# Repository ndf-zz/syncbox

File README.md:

# syncbox

MIDI/USB to DIN sync converter

[work in progress]

## Contents

   - pcb: Kicad schematic and circuit board
   - enclosure: FreeCAD enclosure
   - firmware: STM32 firmware
   - syncbox-edit: Python SysEx configuration editor

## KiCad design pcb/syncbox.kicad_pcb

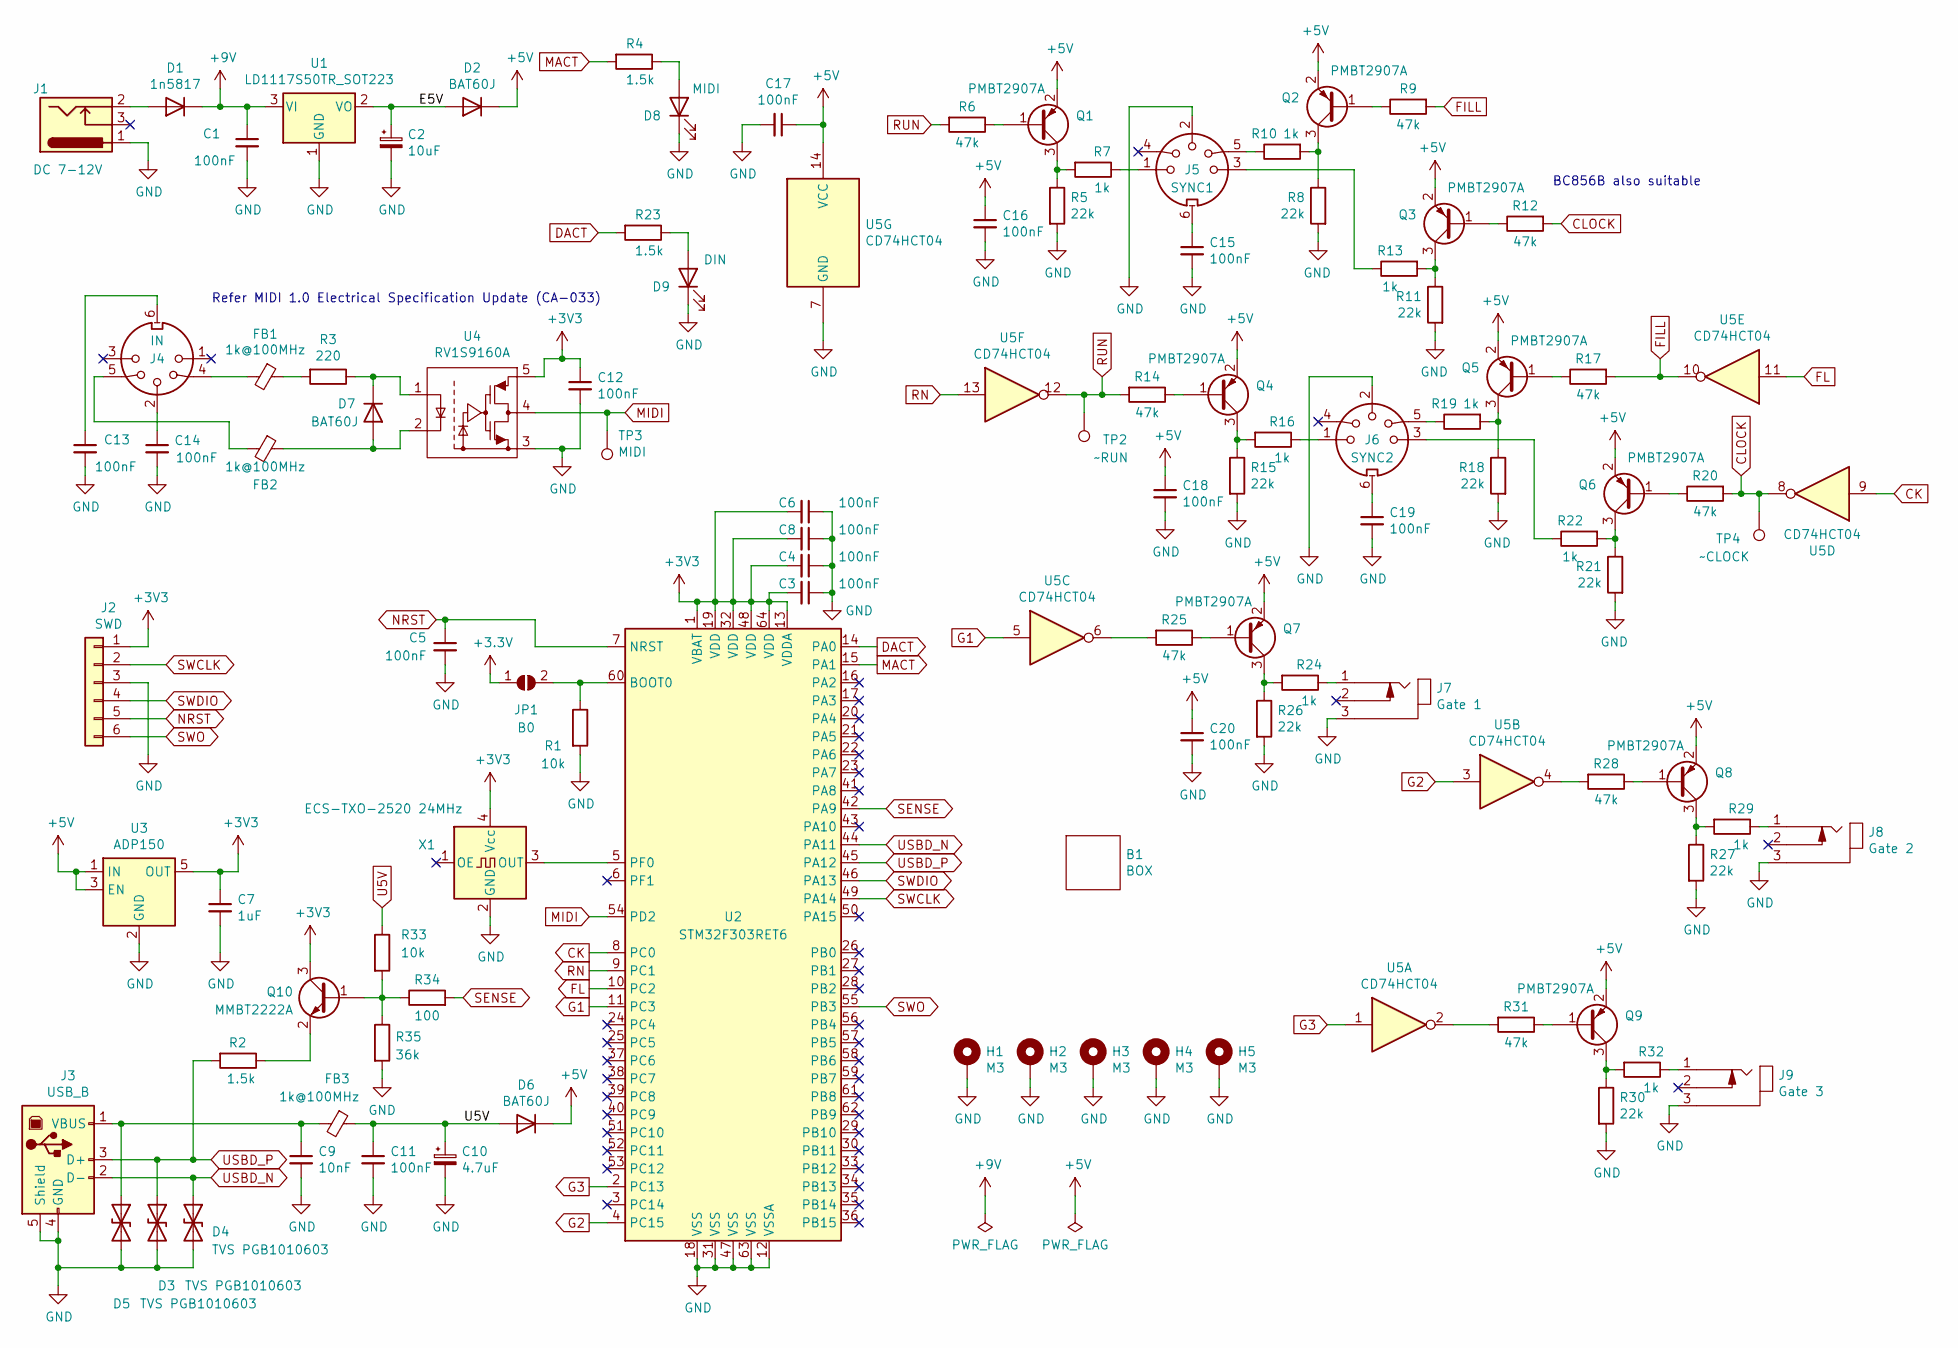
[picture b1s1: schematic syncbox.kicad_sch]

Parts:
B1: BOX
C1, C3, C4, C5, C6, C8, C11, C12, C13, C14, C15, C16, C17, C18, C19, C20: 100nF; C_0805_2012Metric_Pad1.15x1.40mm_HandSolder
C2: 10uF; CP_Radial_D4.0mm_P2.00mm
C7: 1uF; C_0805_2012Metric_Pad1.15x1.40mm_HandSolder
C9: 10nF; C_0805_2012Metric_Pad1.15x1.40mm_HandSolder
C10: 4.7uF; CP_Radial_D4.0mm_P2.00mm
D1: 1n5817; D_A-405_P10.16mm_Horizontal
D2, D6, D7: BAT60J; D_SOD-323_HandSoldering
D3, D4, D5: TVS PGB1010603; D_0603_1608Metric_Pad1.05x0.95mm_HandSolder
D8: MIDI; LED_D3.0mm_Clear
D9: DIN; LED_D3.0mm_Clear
FB1, FB2, FB3: 1k@100MHz; L_0603_1608Metric_Pad1.05x0.95mm_HandSolder
H1, H2, H3, H4, H5: M3; MountingHole_3.2mm_M3_Pad
J1: DC 7-12V; BarrelJack_Horizontal
J2: SWD; PinHeader_1x06_P2.54mm_Vertical
J3: USB_B; MUSBD111M0
J4: IN; 5211450-1
J5: SYNC1; 5211450-1
J6: SYNC2; 5211450-1
J7: Gate 1; 35RAPC2AHN2
J8: Gate 2; 35RAPC2AHN2
J9: Gate 3; 35RAPC2AHN2
JP1: B0; SolderJumper-2_P1.3mm_Open_RoundedPad1.0x1.5mm
Q1, Q2, Q3, Q4, Q5, Q6, Q7, Q8, Q9: PMBT2907A; SOT-23_Handsoldering
Q10: MMBT2222A; SOT-23_Handsoldering
R1: 10k; R_0805_2012Metric_Pad1.15x1.40mm_HandSolder
R2, R4, R23: 1.5k; R_0805_2012Metric_Pad1.15x1.40mm_HandSolder
R3: 220; R_0805_2012Metric_Pad1.15x1.40mm_HandSolder
R5, R8, R11, R15, R18, R21, R26, R27, R30: 22k; R_0805_2012Metric_Pad1.15x1.40mm_HandSolder
R6, R9, R12, R14, R17, R20, R25, R28, R31: 47k; R_0805_2012Metric_Pad1.15x1.40mm_HandSolder
R7, R10, R13, R16, R19, R22, R24, R29, R32: 1k; R_0805_2012Metric_Pad1.15x1.40mm_HandSolder
R33: 10k; R_0805_2012Metric_Pad1.20x1.40mm_HandSolder
R34: 100; R_0805_2012Metric_Pad1.20x1.40mm_HandSolder
R35: 36k; R_0805_2012Metric_Pad1.20x1.40mm_HandSolder
TP2: ~RUN; TestPoint_Pad_D1.5mm
TP3: MIDI; TestPoint_Pad_D1.5mm
TP4: ~CLOCK; TestPoint_Pad_D1.5mm
U1: LD1117S50TR_SOT223; SOT-223-3_TabPin2
U2: STM32F303RET6; LQFP-64_10x10mm_P0.5mm; LCSC C183214
U3: ADP150; SOT-23-5_HandSoldering
U4: RV1S9160A; SO-5_4.4x3.6mm_P1.27mm
U5: CD74HCT04; SOIC-14_3.9x8.7mm_P1.27mm
X1: ECS-TXO-2520 24MHz; Oscillator_SMD_SeikoEpson_SG210-4Pin_2.5x2.0mm_HandSoldering

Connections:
+5V: C16.1, C17.1, C18.1, C20.1, D2.1 (K), D6.1 (K), Q1.2 (E), Q2.2 (E), Q3.2 (E), Q4.2 (E), Q5.2 (E), Q6.2 (E), Q7.2 (E), Q8.2 (E), Q9.2 (E), U3.1 (IN), U3.3 (EN), U5.14 (VCC)
+9V: C1.1, D1.1 (K), U1.3 (VI)
/E5V: C2.1, D2.2 (A), U1.2 (VO)
CK: U2.8 (PC0), U5.9
CLOCK: R12.2, R20.2, TP4.1, U5.8
DACT: R23.2, U2.14 (PA0)
FILL: R9.2, R17.2, U5.10
FL: U2.10 (PC2), U5.11
G1: U2.11 (PC3), U5.5
G2: U2.4 (PC15), U5.3
G3: U2.2 (PC13), U5.1
GND: C1.2, C2.2, C3.1, C4.1, C5.2, C6.1, C7.2, C8.1, C9.2, C10.2, C11.2, C12.2, C13.2, C14.2, C15.2, C16.2, C17.2, C18.2, C19.2, C20.2, D3.2 (A2), D4.2 (A2), D5.2 (A2), D8.1 (K), D9.1 (K), H1.1, H2.1, H3.1, H4.1, H5.1, J1.1, J2.3, J3.4 (GND), J3.5 (Shield), J5.2, J6.2, J7.3, J8.3, J9.3, R1.2, R5.2, R8.2, R11.2, R15.2, R18.2, R21.2, R26.2, R27.2, R30.2, R35.2, U1.1 (GND), U2.12 (VSSA), U2.18 (VSS), U2.31 (VSS), U2.47 (VSS), U2.63 (VSS), U3.2 (GND), U4.3, U5.7 (GND), X1.2 (GND)
MACT: R4.2, U2.15 (PA1)
MIDI: TP3.1, U2.54 (PD2), U4.4
NRST: C5.1, J2.5, U2.7 (NRST)
unnamed: C9.1, D5.1 (A1), FB3.2, J3.1 (VBUS)
unnamed: C13.1, J4.6
unnamed: C14.1, J4.2
unnamed: C15.1, J5.6
unnamed: C19.1, J6.6
unnamed: D1.2 (A), J1.2
unnamed: D7.1 (K), R3.1, U4.1
unnamed: D7.2 (A), FB2.1, U4.2
unnamed: D8.2 (A), R4.1
unnamed: D9.2 (A), R23.1
unnamed: FB1.1, R3.2
unnamed: FB1.2, J4.4
unnamed: FB2.2, J4.5
unnamed: J5.1, R7.1
unnamed: J5.3, R13.1
unnamed: J5.5, R10.1
unnamed: J6.1, R16.1
unnamed: J6.3, R22.1
unnamed: J6.5, R19.1
unnamed: J7.1, R24.1
unnamed: J8.1, R29.1
unnamed: J9.1, R32.1
unnamed: JP1.2 (B), R1.1, U2.60 (BOOT0)
unnamed: Q1.1 (B), R6.1
unnamed: Q1.3 (C), R5.1, R7.2
unnamed: Q2.1 (B), R9.1
unnamed: Q2.3 (C), R8.1, R10.2
unnamed: Q3.1 (B), R12.1
unnamed: Q3.3 (C), R11.1, R13.2
unnamed: Q4.1 (B), R14.1
unnamed: Q4.3 (C), R15.1, R16.2
unnamed: Q5.1 (B), R17.1
unnamed: Q5.3 (C), R18.1, R19.2
unnamed: Q6.1 (B), R20.1
unnamed: Q6.3 (C), R21.1, R22.2
unnamed: Q7.1 (B), R25.1
unnamed: Q7.3 (C), R24.2, R26.1
unnamed: Q8.1 (B), R28.1
unnamed: Q8.3 (C), R27.1, R29.2
unnamed: Q9.1 (B), R31.1
unnamed: Q9.3 (C), R30.1, R32.2
unnamed: Q10.1 (B), R33.2, R34.1, R35.1
unnamed: Q10.2 (E), R2.1
unnamed: R25.2, U5.6
unnamed: R28.2, U5.4
unnamed: R31.2, U5.2
unnamed: U2.5 (PF0), X1.3 (OUT)
RN: U2.9 (PC1), U5.13
RUN: R6.2, R14.2, TP2.1, U5.12
SENSE: R34.2, U2.42 (PA9)
SWCLK: J2.2, U2.49 (PA14)
SWDIO: J2.4, U2.46 (PA13)
SWO: J2.6, U2.55 (PB3)
U5V: C10.1, C11.1, D6.2 (A), FB3.1, R33.1
USBD_N: D4.1 (A1), J3.2 (D-), U2.44 (PA11)
USBD_P: D3.1 (A1), J3.3 (D+), R2.2, U2.45 (PA12)

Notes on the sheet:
Refer MIDI 1.0 Electrical Specification Update (CA-033)
BC856B also suitable

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
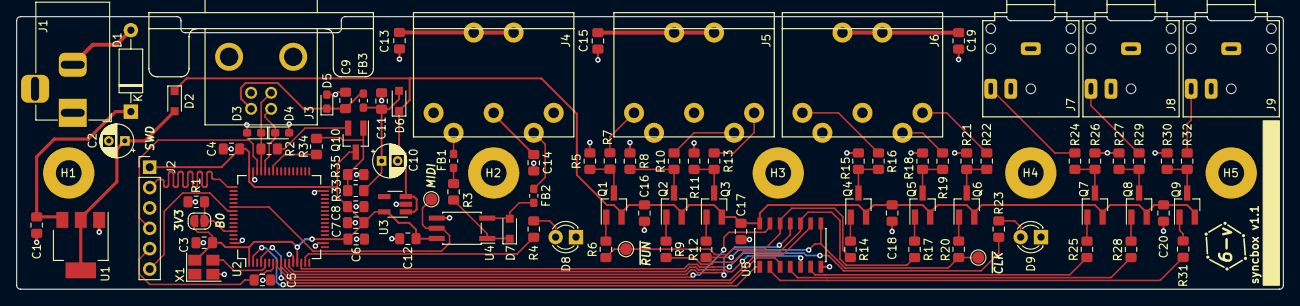
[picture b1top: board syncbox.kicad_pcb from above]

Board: 2 copper layers, 158.0 x 34.0 mm, 102 parts (0 on the bottom side), 72 nets.

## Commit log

2024-04-12 Add cad files to ignore
2024-04-12 Add CAD files
2024-04-12 Add prototype photo
2024-04-12 Add preliminary hardware test
2024-04-18 Add usb-midi diagram
2024-04-22 Add led display code
2024-04-22 Update pin assignment document
2024-04-22 Shuffle system init and update Makefile
2024-04-22 Update test program to use display code
2024-04-22 Version 1.1 hardware changes
2024-04-24 Update MIDI UART and event interfaces
2024-04-24 Update test code for midi event
2024-04-25 Update event buffer handling
2024-04-26 Enable SWO output pin
2024-04-26 Add dorky top label design
2024-04-27 Update schematic and top label
2024-04-28 Move midi stream reader into event interface
2024-04-28 Shuffle main loop into PendSV handler
2024-04-28 Cosmetic shuffling
2024-04-29 Update flash memory plan
2024-04-29 Begin settings, options and config
2024-04-29 Fix typos on flash map
2024-04-30 Remove -fno-common and use gnu format with size
2024-04-30 Update config, settings and flash options
2024-04-30 Update test code to use settings, config and options
2024-05-01 Add sysex configuration handling
2024-05-02 Fix rom/build mismatch sysex error
2024-05-02 Add SWO trace script
2024-05-02 Add trigger length config option
2024-05-03 Add crude timer and improve output handling
2024-05-04 Add USB descriptors to rom options
2024-05-07 Add crude sysex config editor
2024-05-08 Options and config shuffling
2024-05-08 Adjust uptime counter to 1/8ms and add conditional trace
2024-05-08 Write usb serial number on first boot
2024-05-08 Update timeouts for 1/8ms uptime
2024-05-08 Fix timer offset logic
2024-05-08 Start midi-usb device
2024-05-08 Update to match 1/8 ms uptime and add manpage
